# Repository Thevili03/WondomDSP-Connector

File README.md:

# WondomDSP-Connector
Connector board design for CY7C68013A USB programmer.

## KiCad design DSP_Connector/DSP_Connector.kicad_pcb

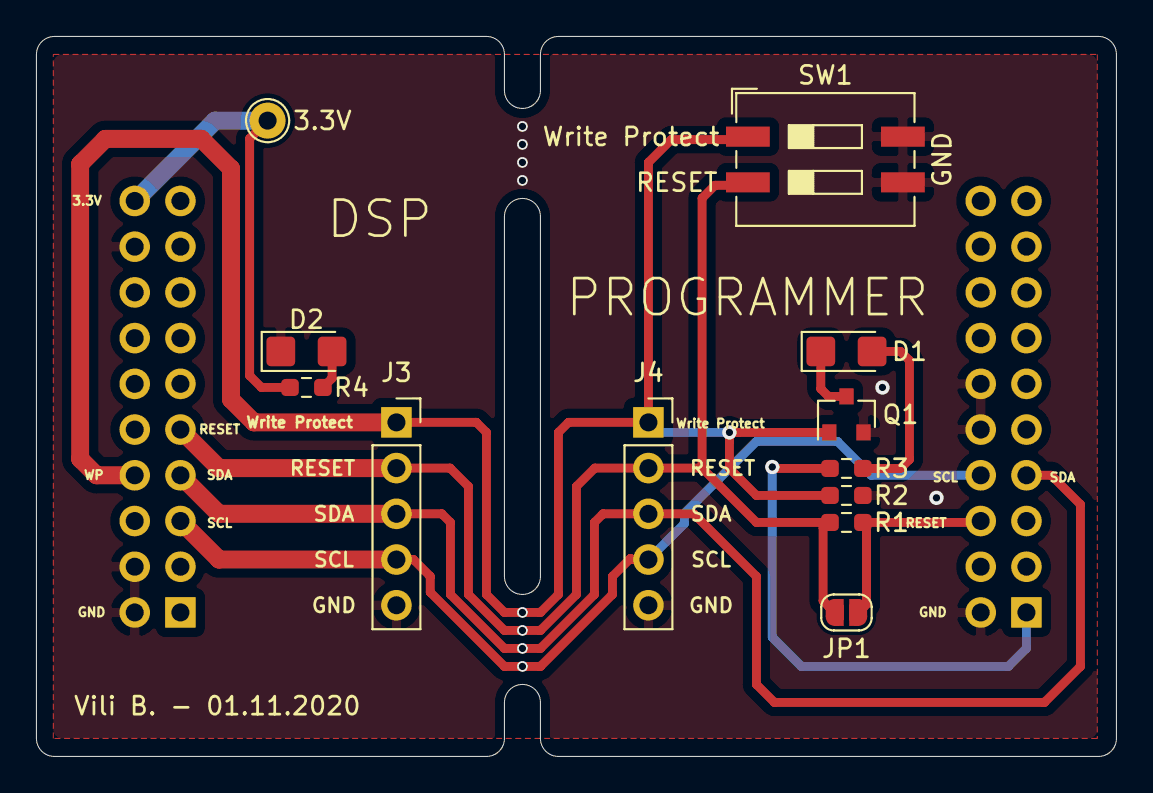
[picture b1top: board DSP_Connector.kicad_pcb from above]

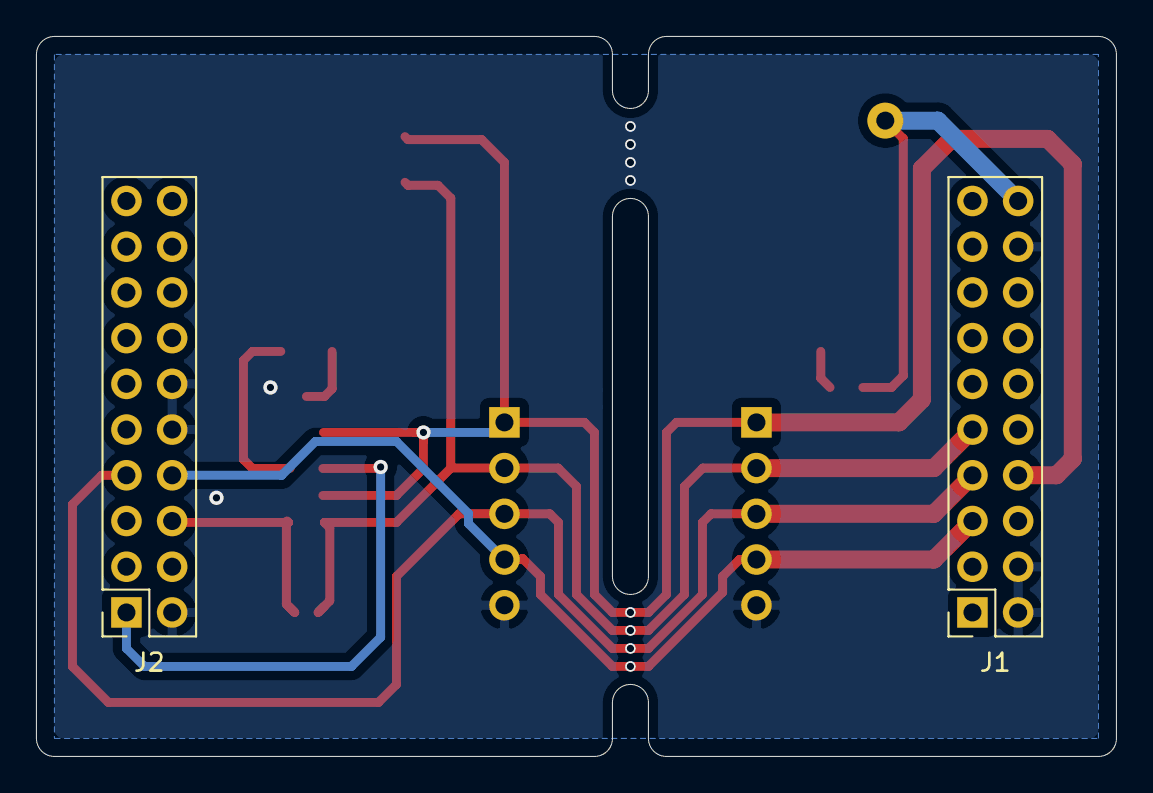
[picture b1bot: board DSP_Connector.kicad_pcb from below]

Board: 2 copper layers, 60.0 x 40.0 mm, 14 parts (2 on the bottom side), 11 nets.

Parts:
D1, D2: LED; LED_1206_3216Metric_Castellated
J1, J2: Conn_02x10_Odd_Even; PinSocket_2x10_P2.54mm_Vertical
J3, J4: Conn_01x05_Male; PinSocket_1x05_P2.54mm_Vertical
JP1: Jumper; SolderJumper-2_P1.3mm_Open_RoundedPad1.0x1.5mm
Q1: BSS123; SOT-23
R1, R2, R3, R4: R_Small; R_0603_1608Metric_Pad0.98x0.95mm_HandSolder
SW1: SW_DIP_x02; SW_DIP_SPSTx02_Slide_9.78x7.26mm_W8.61mm_P2.54mm
TP1: TestPoint; TestPoint_THTPad_D2.0mm_Drill1.0mm

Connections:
+3.3VA: J2.1, R3.1
+3V3: J1.20, R4.1, TP1.1
GND: D2.1, J1.2, J1.4, J1.18, J2.2, J2.10, J2.12, J3.5, J4.5, Q1.2, R2.2, SW1.3, SW1.4
unnamed: D1.1, Q1.3
unnamed: D1.2, R3.2
unnamed: D2.2, R4.2
unnamed: J2.6, JP1.1, R1.2
RESET: J1.9, J3.2, J4.2, JP1.2, R1.1, SW1.2
SCL: J1.5, J2.8, J3.4, J4.4
SDA: J1.7, J2.7, J3.3, J4.3
WP: J1.8, J3.1, J4.1, Q1.1, R2.1, SW1.1

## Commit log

2020-11-01 Create Connector
2021-02-28 Added photos
    Added photos
2021-02-28 Update README.md
    Readme update - added photos
